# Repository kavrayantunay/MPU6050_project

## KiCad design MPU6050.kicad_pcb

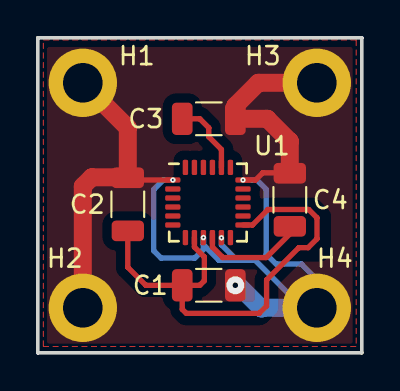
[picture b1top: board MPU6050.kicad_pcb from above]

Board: 2 copper layers, 18.0 x 17.5 mm, 9 parts (0 on the bottom side), 4 nets.

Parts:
C1, C2, C4: 0.1uF; C_1206_3216Metric
C3: 2.2nF; C_1206_3216Metric
H1, H2, H3, H4: MountingHole_Pad; MountingHole_2.2mm_M2_DIN965_Pad
U1: MPU-6050; InvenSense_QFN-24_4x4mm_P0.5mm

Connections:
+3V3: C1.1, C2.1, U1.8 (VDDIO), U1.13 (VDD)
GND: C1.2, C2.2, C3.2, C4.2, H1.1, H2.1, H3.1, H4.1, U1.1 (CLKIN), U1.9 (AD0), U1.11 (FSYNC), U1.18 (GND)
unnamed: C3.1, U1.20 (CPOUT)
unnamed: C4.1, U1.10 (REGOUT)
